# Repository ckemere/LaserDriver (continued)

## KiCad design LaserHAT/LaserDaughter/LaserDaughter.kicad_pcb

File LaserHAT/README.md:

# LaserDriver Pi HAT

A Raspberry Pi HAT for driving laser diodes in neuroscience experiments.
The board sits on top of a Pi, receives trigger pulses that the Pi relays
from experiment software on the network, and produces precisely timed laser
pulses with software-programmable intensity.

---

## Big Picture

The central challenge in optogenetics and fiber-photometry experiments is
getting clean, fast, digitally-controlled laser pulses synchronized to
behavior or electrophysiology acquisition. USB-connected laser drivers
introduce latency and jitter through the OS scheduler; GPIO-connected drivers
are faster but require dedicated single-board computers or FPGAs.

This board solves the problem with a two-layer approach:

1. **A remote experiment machine** (Python / Bonsai / Open Ephys, …) runs
   the high-level logic and decides when a pulse should start. It sends a
   UDP trigger datagram to the Pi.
2. **The Raspberry Pi** runs the broker (`Pi/brokerd/`), whose real-time
   trigger thread turns each datagram into a single GPIO edge as fast as
   possible and ACKs it. The Pi also hosts the OLED and web GUIs for
   setting parameters.
3. **The MSPM0G3507 MCU** on the HAT responds to that edge in hardware,
   generates the PWM waveform with sub-microsecond jitter, and controls the
   laser driver directly.

The remote machine handles "what and when."
The Pi gets the trigger from the network to the HAT with minimal, measured latency.
The MCU handles "how precisely" at the microsecond timescale.

---

## Board Overview

| Item | Value |
|---|---|
| Target Pi | Raspberry Pi 4 |
| Form factor | Raspberry Pi HAT (65 × 56.5 mm) |
| Connector | 40-pin PinSocket on B.Cu (female, mates with Pi's male header) |
| MCU | TI MSPM0G3507SRHBR (U7, VQFN-32, ARM Cortex-M0+) |
| Laser supply | MT3608 boost converter — 5 V → ~12 V |
| UART bridge | CH340N USB-to-UART (USB-C receptacle) |
| Debug port | 5-pin SWD header (NRST / SWCLK / SWDIO / 3V3 / GND) |
| Laser connector | 6-pin shrouded header |

---

## Schematic Hierarchy

The project uses a KiCad hierarchical design with one root sheet and three
child sheets:

```
LaserDriver.kicad_sch          ← root: RPi GPIO header + sheet hierarchy
├── laser_driver_circuit.kicad_sch   ← MT3608 boost + current-steering driver
├── mspm0_controller.kicad_sch       ← MSPM0G3507 + decoupling + SWD header
└── usb_uart.kicad_sch               ← CH340N + USB-C receptacle + solder bridges
```

The root schematic was built from the official RPi HAT template, preserving
every GPIO label and decoupling element exactly.

---

## Power System

### Supply rails

```
Raspberry Pi 5 V (Pin 2/4)
    │
    ├──▶ MT3608 boost converter ──▶ +LASER_V (~12 V) ──▶ laser diode anode
    │
    └──▶ Pi 3.3 V (Pin 1/17) ─── P-MOSFET switch ──▶ VCC_3V3_MCU ──▶ MSPM0
```

The MCU is **not** powered directly from the always-on 3.3 V rail.  Instead,
a P-channel MOSFET controlled by **GPIO23** (`MCU_POWER_EN`) acts as a
software power switch. This allows the Pi to hard-reset the MCU by toggling
GPIO23 low. `Pi/power_cycle.py` does this before every flash
(`laserhat-flash`, `make flash`), and it is also useful for fault recovery.

### MT3608 boost converter

The MT3608 (SOT-23-6) is a fixed-frequency current-mode boost controller.
On this board it is configured to produce ~12 V from the Pi's 5 V rail using
a standard resistor divider on the feedback pin (BOOST_FB).

Key signals in `laser_driver_circuit.kicad_sch`:

| Net | Description |
|---|---|
| `VCC_5V_IN` | 5 V input from Pi (VBUS via GPIO header) |
| `BOOST_SW` | Inductor switching node (do not probe with a scope ground clip) |
| `BOOST_FB` | Resistor divider feedback to MT3608 FB pin |
| `BOOST_EN` | Enable pin — pulled high, can be driven low to shut down boost |
| `+LASER_V` | ~12 V output — laser diode anode supply |

Input and output decoupling capacitors are placed close to the MT3608 on the
PCB layout; do not move them during placement.

---

## Laser Driver Circuit

The driver uses a **current-steering PWM topology** with a matched dual
N-MOSFET pair (BSS138DW, SOT-363).

```
+LASER_V ──▶ [Laser Diode] ──▶ [Q_main] ──▶ GND   (PWM_LASER = high → lasing)
+LASER_V ──▶ [Dummy Load ] ──▶ [Q_dummy] ──▶ GND   (PWM_DUMMY = high → dark)
```

`PWM_LASER` and `PWM_DUMMY` are always complementary: when the laser is
off, current flows through the dummy load instead of turning off abruptly.
This keeps the supply voltage stable and prevents the inductive spike from
the laser diode bond wire from coupling back into the supply.

A **TLV2371** rail-to-rail op-amp provides a feedback path for DC bias
control.  The MCU's **DAC output (VREF)** sets the target current; the
op-amp closes the loop by adjusting gate drive on Q_main.

### Component choices

- **Q2 (dual MOSFET pair):** BSS138DW (SOT-363) for matched threshold
  voltage. The schematic notes that `Si1902DL` (1.25 A rated) is required for
  high-power red lasers; the BSS138DW is adequate for lower-power blue lasers.
- **Laser connector:** 6-pin shrouded header (J_LASER) carries
  `+LASER_V`, `GND`, `PWM_LASER`, `PWM_DUMMY`, `VREF`, and `ADC` (monitor).
- **SolderJumper SJ1:** bypasses the op-amp feedback path for open-loop
  testing. Install closed only during calibration.

---

## MSPM0G3507 Controller

The MSPM0G3507SRHBR (U7, VQFN-32) is a Cortex-M0+ with hardware timers, a
12-bit DAC, and SWD debug — all necessary for this application. (The 48-pin
IC1 footprint on the sheet is not populated.)

### GPIO assignments

Pins used by the firmware (`Firmware/board.h`; the full pin-by-pin map,
including unused pins, is in `gpio_design.md` §2):

| MSPM0 pin | Net | Direction | Description |
|---|---|---|---|
| PA21 | `PWM_LASER` | output | TIMA0_CCP0 — laser PWM |
| PA22 | `PWM_DUMMY` | output | TIMA0_CCP0_CMPL — hardware complement of PA21 |
| PA15 | `MSPM0_DAC` | output | DAC0_OUT — laser current setpoint |
| PA14 | `STIM_TRIGGER` | input | BNC trigger, rising edge (internal pull-down) |
| PA19 | `MSPM0_SWDIO` | bidirectional → input | SWD data during the ~4 s boot blink, then the **Pi trigger input** (← Pi GPIO 24, rising edge, pull-down) |
| PA20 | `MSPM0_SWCLK` | input | SWD clock (← Pi GPIO 25) |
| PA13 | `STIM_MIRROR` | output | Stimulus mirror / boot-blink indicator; EStim output |
| PA3–PA6 | `BUTTON1`–`BUTTON4` | input | Front-panel buttons (active-high, pull-down) |
| PA10 | `MCU_UART_TX` | output | UART0 TX → Pi GPIO15 / CH340N |
| PA11 | `MCU_UART_RX` | input | UART0 RX ← Pi GPIO14 / CH340N |
| NRST | `MSPM0_NRST` | input | Reset (← Pi GPIO 18 and the SWD header) |
| VDD | `MSPM0_3V3` | power | Switched 3.3 V from Pi (GPIO23 P-MOSFET) |
| VSS / EPAD | `GND` | power | Ground |

### Decoupling

Five 100 nF capacitors are placed on the MCU's VDD/VDDA/VSS/VSSA pins.
Their placement on the PCB layout is critical — keep them within 1 mm of
the MCU pads.

### SWD debug header (J_SWD, 5-pin, 1.27 mm pitch)

| Pin | Signal |
|---|---|
| 1 | NRST |
| 2 | SWCLK |
| 3 | SWDIO |
| 4 | 3.3 V |
| 5 | GND |

OpenOCD with a CMSIS-DAP probe is recommended for firmware flashing.

---

## USB/UART Interface

The USB-C connector and CH340N bridge serve two purposes depending on
hardware configuration:

### Mode 1 — Pi-controlled (normal operation)

Solder bridges **SB1 and SB2 are removed** (open, factory default).

The Pi communicates with the MSPM0 directly over its own UART
(GPIO14 = TX, GPIO15 = RX).  The CH340N is powered down (no USB cable
connected).  The MCU receives experiment parameters (pulse width,
intensity, timing mode) from Pi userspace, then fires autonomously on a
trigger edge: Pi GPIO 24 → PA19 (network triggers relayed by the broker),
the BNC input on PA14, or button 1.

### Mode 2 — Standalone / development (USB-C active)

Solder bridges **SB1 and SB2 are installed** (closed).

A USB-C cable connects a laptop directly to the CH340N, which presents
as a virtual COM port.  The CH340N bridges USB to the MSPM0's UART.
This mode is used for:
- Firmware development without a Pi attached
- Interactive calibration and testing
- Updating pulse parameters from a laptop in the rig

**Do not connect USB-C and Pi UART simultaneously** — both would drive the
same TX/RX lines and contention will damage one of the drivers.

### USB-C UFP detection

Two 5.1 kΩ pull-down resistors on CC1 and CC2 identify the board as a
USB device (UFP) to the host.  This is required by the USB-C specification
for Type-C cables to deliver power — without them, some hosts will not
enumerate the device.

### CH340N power

The CH340N is powered from VBUS_5V (the USB-C VBUS pin) through a
decoupling capacitor.  When no USB cable is connected the chip is
unpowered, drawing no current from the Pi's 5 V rail.

---

## Raspberry Pi GPIO Usage

Pins the Pi software drives (the full header map from the schematic,
including the legacy eink SPI wiring the software no longer uses, is in
`gpio_design.md` §1):

| Pi GPIO | Pin | Function |
|---|---|---|
| GPIO14 (TXD) | Pin 8 | UART TX → MCU RX (PA11) — `/dev/ttyS0`, owned by the broker |
| GPIO15 (RXD) | Pin 10 | UART RX ← MCU TX (PA10) |
| GPIO18 | Pin 12 | MCU NRST (flashing) |
| GPIO23 | Pin 16 | MCU power switch (`MCU_POWER_EN`, P-MOSFET gate) |
| GPIO24 | Pin 18 | **Trigger** → MCU PA19 (driven by the broker); SWDIO while flashing |
| GPIO25 | Pin 22 | SWCLK → MCU PA20 (flashing) |
| GPIO0 / GPIO1 | Pin 27 / 28 | HAT ID EEPROM (I²C) |
| GPIO2 / GPIO3, GPIO4 | Pin 3 / 5, 7 | Adafruit OLED bonnet (I²C, reset) — not used by the HAT itself |
| 5 V | Pin 2/4 | Laser supply rail (MT3608 input) |
| 3.3 V | Pin 1/17 | MCU power (via the GPIO23 P-MOSFET switch) |

---

## Net Naming Conventions

| Net | Description |
|---|---|
| `VCC_5V_IN` | 5 V from Pi GPIO header |
| `+LASER_V` | ~12 V boost output (laser anode supply) |
| `VCC_3V3_MCU` | Switched 3.3 V to MCU |
| `VBUS_5V` | USB-C VBUS (powers CH340N only) |
| `PWM_LASER` | Laser PWM (MCU → driver Q_main gate) |
| `PWM_DUMMY` | Complementary dummy-load PWM |
| `VREF` | DAC output — laser current setpoint |
| `STIM_TRIGGER` | BNC trigger → MCU PA14 |
| `MSPM0_SWDIO` | Pi GPIO24 ↔ MCU PA19: SWD data, then the Pi trigger line |
| `UART_TX/RX` | MCU ↔ CH340N or Pi UART |
| `SWCLK/SWDIO` | SWD debug bus |

---

## Repository layout (Rev 2, 2026-10)

Three KiCad 9 projects, hand-placed and hand-routed:

- `LaserDriver.kicad_pro` — the HAT (this directory; sheets `mspm0_controller`, `usb_uart`, `bnc_daughter_io`).
- `LaserDaughter/` — the laser-diode output module (plugs into J8/J9).
- `EStimDaughter/` — the isolated e-stim output module (schematic generated by `gen_schematic.py`; interface in
  `estim_interface/ESTIM_MODULE_SPEC.md`).

`REV2_NOTES.md` has the Rev 2 design history and the current MCU pin map, `CLAUDE.md` the working rules and tool
list, `fab/` the JLC order files (`tools/jlc_fab.py`) and `fab/orders/` the archives actually ordered. The sections
above describe the circuits; where they disagree with `REV2_NOTES.md` on pins, REV2_NOTES is current.

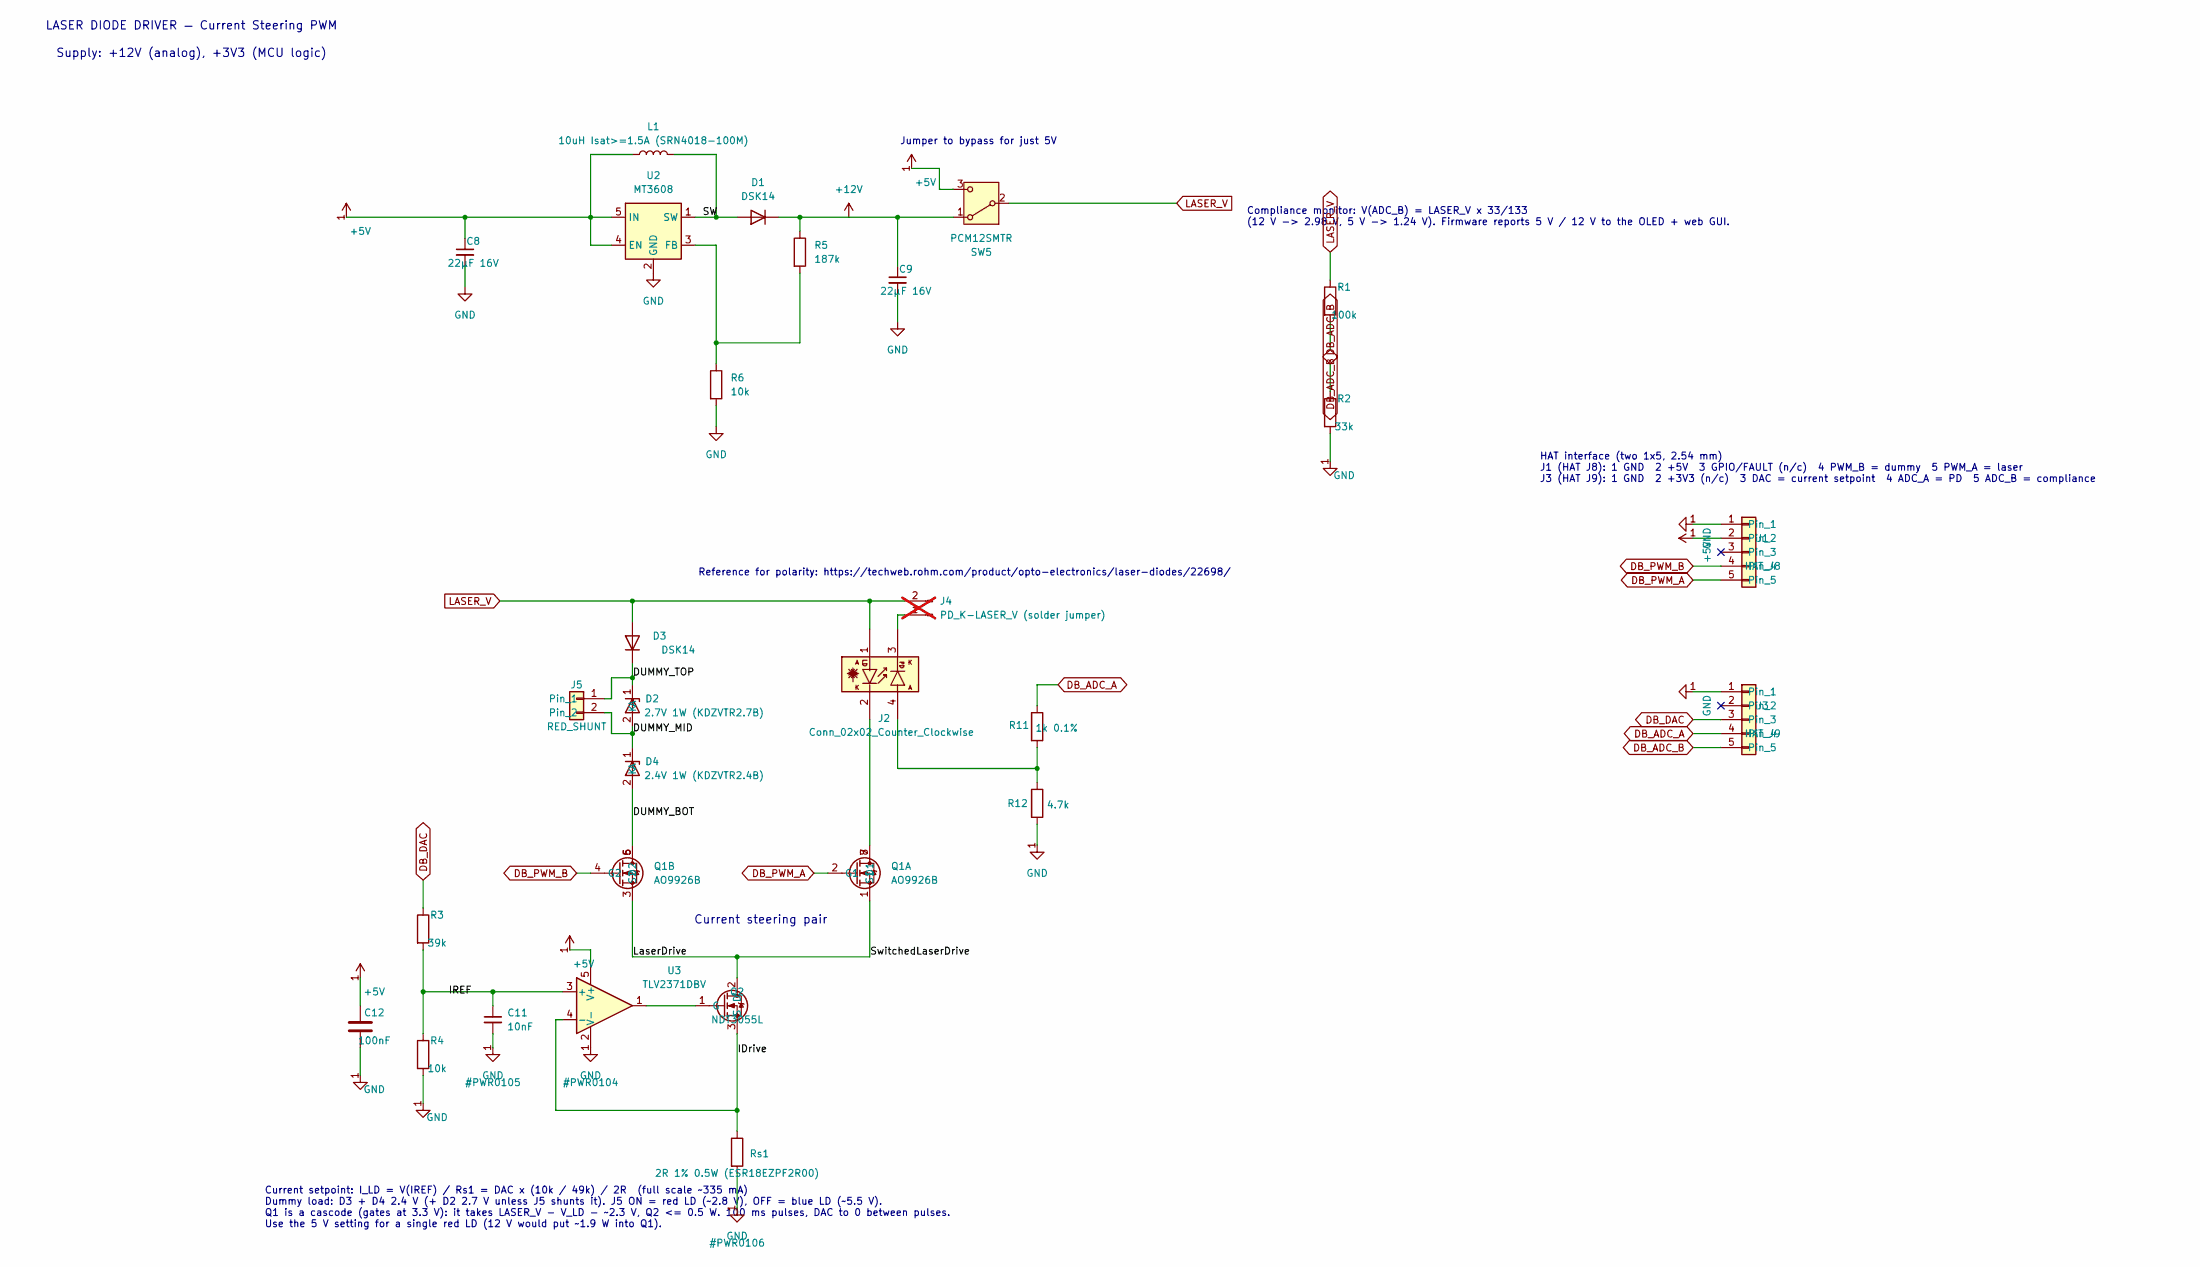
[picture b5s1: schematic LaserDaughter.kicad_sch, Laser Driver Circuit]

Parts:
C8, C9: 22µF 16V; C_1206_3216Metric; LCSC Part # C12891
C11: 10nF; C_0402_1005Metric; LCSC Part # C15195
C12: 100nF; C_0402_1005Metric; LCSC Part # C307331
D1, D3: DSK14; D_SOD-123F; LCSC Part # C37049
D2: 2.7V 1W (KDZVTR2.7B); D_SOD-123F; LCSC Part # C209583
D4: 2.4V 1W (KDZVTR2.4B); D_SOD-123F; LCSC Part # C209582
J1: HAT_J8; PinHeader_1x05_P2.54mm_Vertical
J2: Conn_02x02_Counter_Clockwise; PinHeader_2x02_P2.54mm_Vertical
J3: HAT_J9; PinHeader_1x05_P2.54mm_Vertical
J4: PD_K-LASER_V (solder jumper); SolderJumper-2_P1.3mm_Open_RoundedPad1.0x1.5mm; not fitted
J5: RED_SHUNT; PinHeader_1x02_P2.00mm_Vertical
L1: 10uH Isat>=1.5A (SRN4018-100M); L_Bourns-SRN4018; LCSC Part # C503307
Q1: AO9926B; SOIC-8_3.9x4.9mm_P1.27mm; LCSC Part # C428343
Q2: NDT3055L; SOT-223-3_TabPin2; LCSC Part # C274612
R1: 100k; R_0402_1005Metric; LCSC Part # C25741
R2: 33k; R_0402_1005Metric; LCSC Part # C25779
R3: 39k; R_0402_1005Metric; LCSC Part # C25783
R4, R6: 10k; R_0402_1005Metric; LCSC Part # C25744
R5: 187k; R_0402_1005Metric; LCSC Part # C25761
R11: 1k 0.1%; R_0402_1005Metric; LCSC Part # C852624
R12: 4.7k; R_0402_1005Metric; LCSC Part # C25900
Rs1: 2R 1% 0.5W (ESR18EZPF2R00); R_1206_3216Metric; LCSC Part # C2105197
SW5: PCM12SMTR; SW_SPDT_PCM12; LCSC Part # C221841
U2: MT3608; SOT-23-6; LCSC Part # C84817
U3: TLV2371DBV; SOT-23-5; LCSC Part # C55940

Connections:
+5V: C8.1, C12.1, J1.2, L1.1, SW5.3 (C), U2.4 (EN), U2.5 (IN), U3.5 (V+)
+12V: C9.1, D1.1 (K), R5.1, SW5.1 (A)
/DUMMY_BOT: D4.2 (A), Q1.5 (D2), Q1.6 (D2)
/DUMMY_MID: D2.2 (A), D4.1 (K), J5.2
/DUMMY_TOP: D2.1 (K), D3.1 (K), J5.1
/IDrive: Q2.3 (S), Rs1.1, U3.4 (-)
/IREF: C11.1, R3.2, R4.1, U3.3 (+)
/LaserDrive: Q1.1 (S1), Q1.3 (S2), Q2.2 (D)
/SW: D1.2 (A), L1.2, U2.1 (SW)
DB_ADC_A: J3.4, R11.1
DB_ADC_B: J3.5, R1.2, R2.1
DB_DAC: J3.3, R3.1
DB_PWM_A: J1.5, Q1.2 (G1)
DB_PWM_B: J1.4, Q1.4 (G2)
GND: C8.2, C9.2, C11.2, C12.2, J1.1, J3.1, R2.2, R4.2, R6.2, R12.2, Rs1.2, U2.2 (GND), U3.2 (V-)
LASER_V: D3.2 (A), J2.1 (LD_Anode), J4.2, R1.1, SW5.2 (B)
unnamed: J2.2 (LD_Cathode), Q1.7 (D1), Q1.8 (D1)
unnamed: J2.4 (PD_Anode), R11.2, R12.1
unnamed: J2.3 (PD_Cathode), J4.1
unnamed: Q2.1 (G), U3.1
unnamed: R5.2, R6.1, U2.3 (FB)

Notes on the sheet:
Supply: +12V (analog), +3V3 (MCU logic)
Current steering pair
HAT interface (two 1x5, 2.54 mm) J1 (HAT J8): 1 GND 2 +5V 3 GPIO/FAULT (n/c) 4 PWM_B = dummy 5 PWM_A = laser J3 (HAT J9): 1 GND 2 +3V3 (n/c) 3 DAC = current setpoint 4 ADC_A = PD 5 ADC_B = compliance
LASER DIODE DRIVER — Current Steering PWM
Compliance monitor: V(ADC_B) = LASER_V x 33/133 (12 V -> 2.98 V, 5 V -> 1.24 V). Firmware reports 5 V / 12 V to the OLED + web GUI.
Reference for polarity: https://techweb.rohm.com/product/opto-electronics/laser-diodes/22698/
Current setpoint: I_LD = V(IREF) / Rs1 = DAC x (10k / 49k) / 2R (full scale ~335 mA) Dummy load: D3 + D4 2.4 V (+ D2 2.7 V unless J5 shunts it). J5 ON = red LD (~2.8 V), OFF = blue LD (~5.5 V). Q1 is a cascode (gates at 3.3 V): it takes LASER_V - V_LD - ~2.3 V, Q2 <= 0.5 W. 100 ms pulses, DAC to 0 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
Jumper to bypass for just 5V

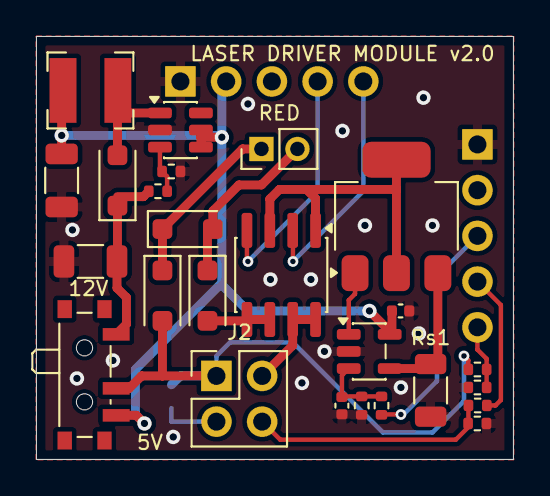
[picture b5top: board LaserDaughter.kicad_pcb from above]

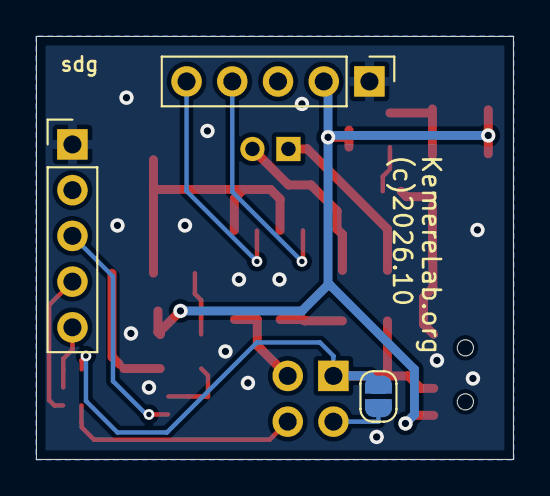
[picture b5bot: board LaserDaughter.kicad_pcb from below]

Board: 2 copper layers, 26.5 x 23.5 mm, 28 parts (3 on the bottom side), 21 nets.

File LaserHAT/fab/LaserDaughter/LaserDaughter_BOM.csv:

Comment,Designator,Footprint,LCSC Part #
10nF,C11,C_0402_1005Metric,C15195
100nF,C12,C_0402_1005Metric,C307331
22µF 16V,"C8,C9",C_1206_3216Metric,C12891
DSK14,"D1,D3",D_SOD-123F,C37049
2.7V 1W (KDZVTR2.7B),D2,D_SOD-123F,C209583
2.4V 1W (KDZVTR2.4B),D4,D_SOD-123F,C209582
10uH Isat>=1.5A (SRN4018-100M),L1,L_Bourns-SRN4018,C503307
AO9926B,Q1,SOIC-8_3.9x4.9mm_P1.27mm,C428343
NDT3055L,Q2,SOT-223-3_TabPin2,C274612
100k,R1,R_0402_1005Metric,C25741
1k 0.1%,R11,R_0402_1005Metric,C852624
4.7k,R12,R_0402_1005Metric,C25900
33k,R2,R_0402_1005Metric,C25779
39k,R3,R_0402_1005Metric,C25783
10k,"R4,R6",R_0402_1005Metric,C25744
187k,R5,R_0402_1005Metric,C25761
2R 1% 0.5W (ESR18EZPF2R00),Rs1,R_1206_3216Metric,C2105197
PCM12SMTR,SW5,SW_SPDT_PCM12,C221841
MT3608,U2,SOT-23-6,C84817
TLV2371DBV,U3,SOT-23-5,C55940

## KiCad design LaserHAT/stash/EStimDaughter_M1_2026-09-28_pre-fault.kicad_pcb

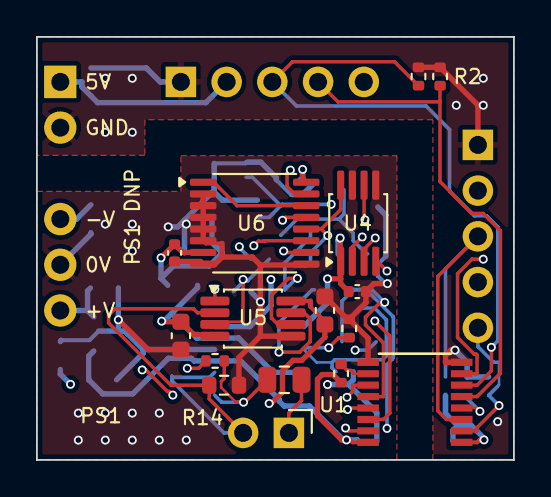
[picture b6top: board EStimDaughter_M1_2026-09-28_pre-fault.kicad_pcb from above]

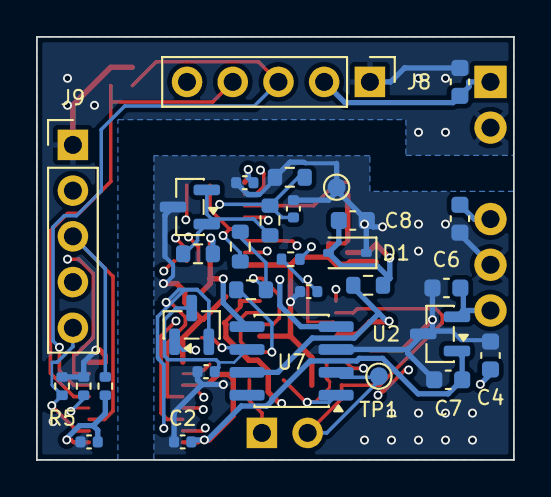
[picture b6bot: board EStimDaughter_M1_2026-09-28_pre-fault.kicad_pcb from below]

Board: 4 copper layers, 26.5 x 23.5 mm, 48 parts (31 on the bottom side), 33 nets.

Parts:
C1, C2, C10, C13, C14: 100n; C_0402_1005Metric
C3: 4.7u; C_0603_1608Metric
C4, C5, C6, C7, C8: 1u 50V; C_0603_1608Metric
C9: 10n; C_0402_1005Metric
C11, C12: 100n; C_0603_1608Metric
C15: 100p; C_0402_1005Metric
C16: 1u 50V; C_0805_2012Metric
C17: 2.2n; C_0402_1005Metric
D1: BZT52C4V7S; D_SOD-323
D2: BAT54C; SOT-23
J1: ELECTRODE E1/E2; PinHeader_1x02_P2.54mm_Horizontal
J8: J8 power/timing (underside); PinHeader_1x05_P2.54mm_Vertical
J9: J9 analog/SPI (underside); PinHeader_1x05_P2.54mm_Vertical
PS1: A0515S-1WR3; DCDC_SIP6_A0515S
R1, R2, R3, R4, R5, R15: 100k; R_0402_1005Metric
R6, R7: 1.5k; R_0603_1608Metric
R8: 15.0k 0.1%; R_0603_1608Metric
R9, R10, R11: 10.0k 0.1%; R_0603_1608Metric
R12: 1k; R_0402_1005Metric
R13: 47; R_0402_1005Metric
R14: 2.00k 0.1%; R_0603_1608Metric
R19: 4.7k; R_0402_1005Metric
TP1: ISENSE; TestPoint_Pad_D1.0mm
TP2: GND_ISO; TestPoint_Pad_D1.0mm
U1: ISO7761FDBQR; SSOP-16_3.9x4.9mm_P0.635mm
U2: TLV76050DBZR; SOT-23
U3: TL431 (2.5V); SOT-23
U4: MCP4921-E/MS; MSOP-8_3x3mm_P0.65mm
U5: OPA2192IDGKR; VSSOP-8_3x3mm_P0.65mm
U6: 74HC4053PW; TSSOP-16_4.4x5mm_P0.65mm
U7: DG419DY; SOIC-8_3.9x4.9mm_P1.27mm

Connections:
+3V3_H: C1.1, J9.2, R3.1, U1.1
+5V_H: C3.1, J8.2, PS1.1
+5V_ISO: C2.1, C7.1, C10.1, C13.1, R7.1, R19.1, U1.16, U2.1, U4.1, U6.16, U7.5
+V_STIM: C4.1, C6.1, C11.1, PS1.6, U2.2, U5.8, U7.4
-5V_ISO: C8.2, C14.2, D1.2, R6.1, U6.7
-V_STIM: C5.2, C12.2, PS1.4, R6.2, U5.4, U7.7
CATH: D2.2, U1.12, U6.11
CATH_H: J8.4, R2.1, U1.5
CS_H: J9.3, R3.2, U1.3
CS_n: U1.14, U4.2
E1: C16.1, R13.2, U7.1
EN: D2.1, U1.11, U6.10
EN_H: J8.3, R1.1, U1.6
FAULT_H: J8.5, U1.7
FAULT_n: R19.2, U1.10
GND_H: C1.2, C3.2, J8.1, J9.1, PS1.2, R1.2, R2.2, R4.2, R5.2, U1.8
GND_ISO: C2.2, C4.2, C5.1, C6.2, C7.2, C8.1, C9.2, C10.2, C11.2, C12.1, C13.2, C14.1, C15.2, C17.2, D1.1, PS1.5, R9.2, R14.2, R15.2, TP2.1, U1.9, U2.3, U3.3, U4.5, U4.7, U5.5, U6.2, U6.3, U6.4, U6.5, U6.6, U6.8, U6.9, U7.3
HOLD: C17.1, D2.3, R15.1, U7.6
ISENSE: J1.2, R14.1, TP1.1, U5.2, U7.2
MOSI: U1.15, U4.4
MOSI_H: J9.5, R5.1, U1.2
unnamed: C16.2, J1.1
unnamed: R13.1, U5.1
unnamed: R7.2, R8.1, U3.1, U3.2
unnamed: R10.1, U4.8, U6.12
unnamed: C9.1, R8.2, R9.1, U4.6
unnamed: C15.1, R12.2, U5.3
unnamed: R10.2, R11.1, U5.6
unnamed: R11.2, U5.7, U6.13
SCK: U1.13, U4.3
SCK_H: J9.4, R4.1, U1.4
SW_P: U6.1, U6.14
V_IN: R12.1, U6.15

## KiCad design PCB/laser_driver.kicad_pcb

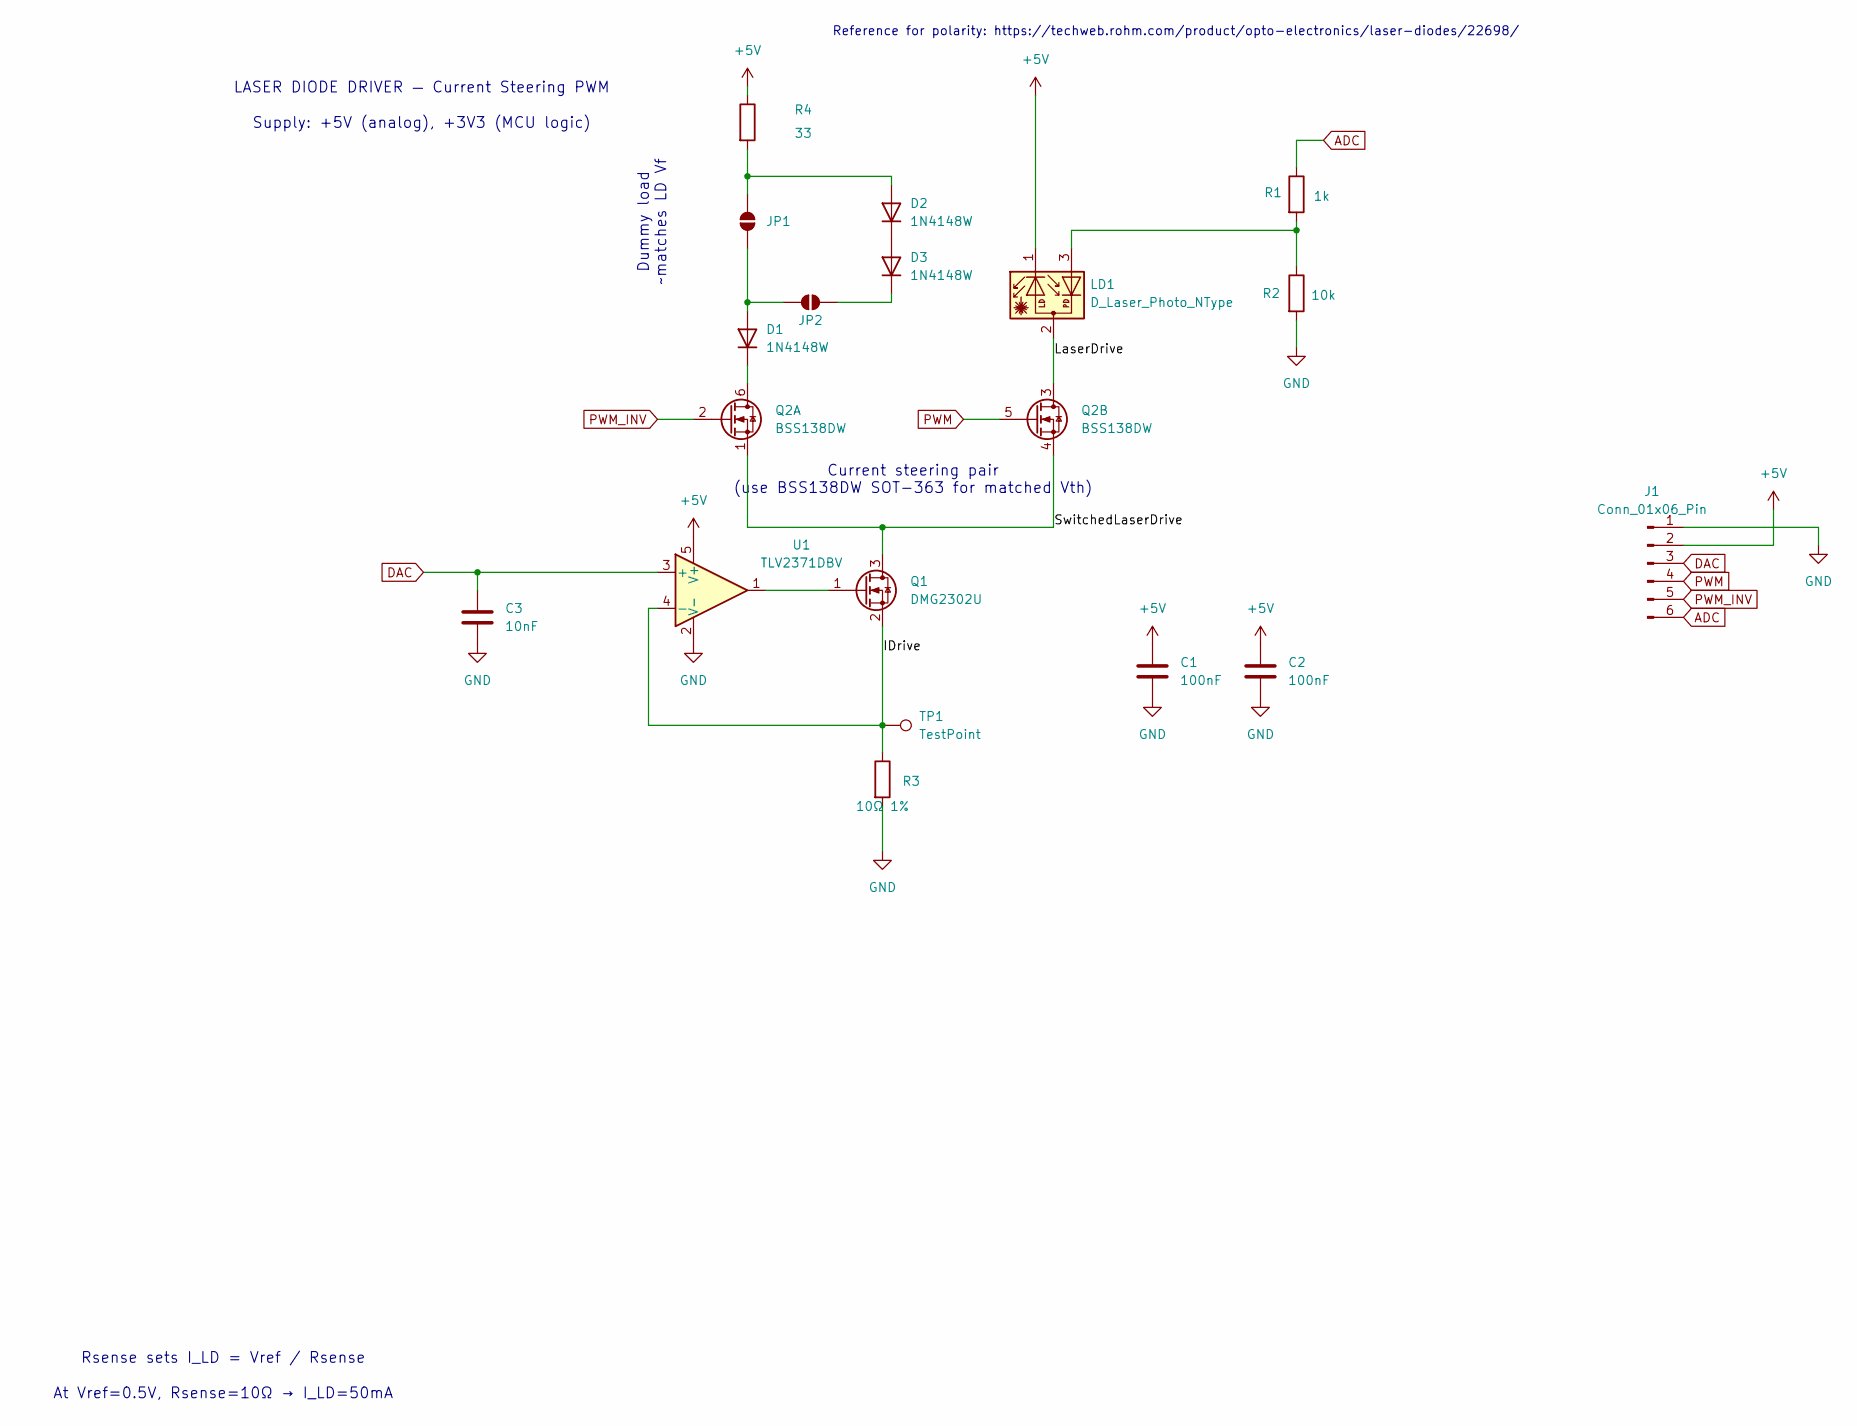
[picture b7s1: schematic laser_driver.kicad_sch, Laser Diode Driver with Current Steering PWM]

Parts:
C1, C2: 100nF; C_0402_1005Metric
C3: 10nF; C_0402_1005Metric
D1, D2, D3: 1N4148W; D_SOD-123
J1: Conn_01x06_Pin; PinHeader_1x06_P2.54mm_Vertical
JP1, JP2: SolderJumper-2_P1.3mm_Open_TrianglePad1.0x1.5mm
LD1: D_Laser_Photo_NType; PinHeader_1x03_P2.54mm_Vertical
Q1: DMG2302U; SOT-23
Q2: BSS138DW; SOT-363_SC-70-6
R1: 1k; R_0402_1005Metric
R2: 10k; R_0402_1005Metric
R3: 10Ω 1%; R_0402_1005Metric
R4: 33; R_0402_1005Metric
TP1: TestPoint; PinHeader_1x01_P2.54mm_Vertical
U1: TLV2371DBV; SOT-23-5

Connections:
+5V: C1.1, C2.1, J1.2, LD1.1, R4.1, U1.5 (V+)
/IDrive: Q1.2 (S), R3.1, TP1.1, U1.4 (-)
/LaserDrive: LD1.2, Q2.3 (D)
/SwitchedLaserDrive: Q1.3 (D), Q2.1 (S), Q2.4 (S)
ADC: J1.6, R1.1
DAC: C3.1, J1.3, U1.3 (+)
GND: C1.2, C2.2, C3.2, J1.1, R2.2, R3.2, U1.2 (V-)
unnamed: D1.2 (A), JP1.2 (B), JP2.2 (B)
unnamed: D1.1 (K), Q2.6 (D)
unnamed: D2.2 (A), JP1.1 (A), R4.2
unnamed: D2.1 (K), D3.2 (A)
unnamed: D3.1 (K), JP2.1 (A)
unnamed: LD1.3, R1.2, R2.1
unnamed: Q1.1 (G), U1.1
PWM: J1.4, Q2.5 (G)
PWM_INV: J1.5, Q2.2 (G)

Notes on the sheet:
Supply: +5V (analog), +3V3 (MCU logic)
Current steering pair (use BSS138DW SOT-363 for matched Vth)
Dummy load ~matches LD Vf
Rsense sets I_LD = Vref / Rsense
LASER DIODE DRIVER — Current Steering PWM
Reference for polarity: https://techweb.rohm.com/product/opto-electronics/laser-diodes/22698/
At Vref=0.5V, Rsense=10Ω → I_LD=50mA

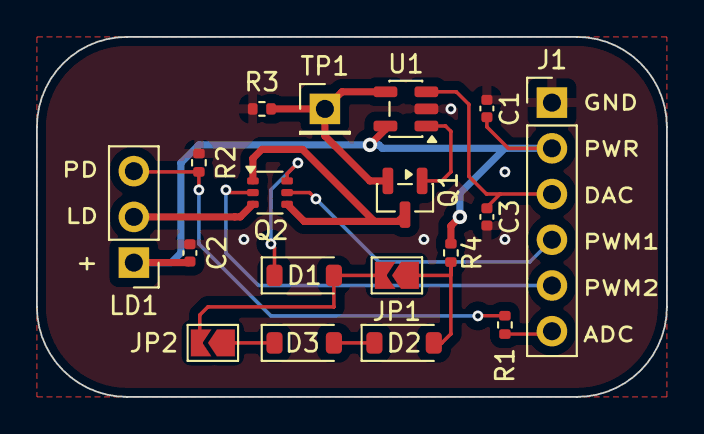
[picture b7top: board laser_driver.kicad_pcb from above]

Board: 2 copper layers, 35.0 x 20.0 mm, 18 parts (0 on the bottom side), 16 nets.

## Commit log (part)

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2026-04-27 Initial Commit of PCB
2026-04-27 Added firmware and examples
2026-04-27 Add complementary PWM modulation to laser driver firmware
    Adds a TIMA0-based complementary PWM output pair on PA12/PA13 (J4
    header pins) to drive the H-bridge gates Q2a/Q2b in the current
    steering topology described in PCB/DESIGN_NOTES.md.
    Configuration:
    - TIMA0, CC0 channel with native CCP0/CCP0N complementary outputs
    - Clock: BUSCLK = 32 MHz, prescale = 1
2026-04-27 Updates for full on vibing
2026-04-27 Added a newline to end of CLAUDE.md
2026-04-27 Updated CLAUDE.md
2026-04-29 Fixed Claude errors, including correcting laser off GPIO settings and fixing initial GPIO state. Updated instructions.
2026-04-29 Added rpi template
2026-05-01 Really added template this time
2026-05-01 Removed incorrect template
2026-05-01 Added hat template files to this branch
2026-05-06 Updates with lots of manual work
2026-05-09 Updates to design, finalized PCB layout
2026-05-15 Updated project for manufacturing. Should merge branch if/when we get back a working product
2026-06-02 Added laserHat firmware rev 0.1
2026-06-03 Added firmware
2026-06-03 Removed old draft firmware
2026-06-04 Add audit-derived TODO list
